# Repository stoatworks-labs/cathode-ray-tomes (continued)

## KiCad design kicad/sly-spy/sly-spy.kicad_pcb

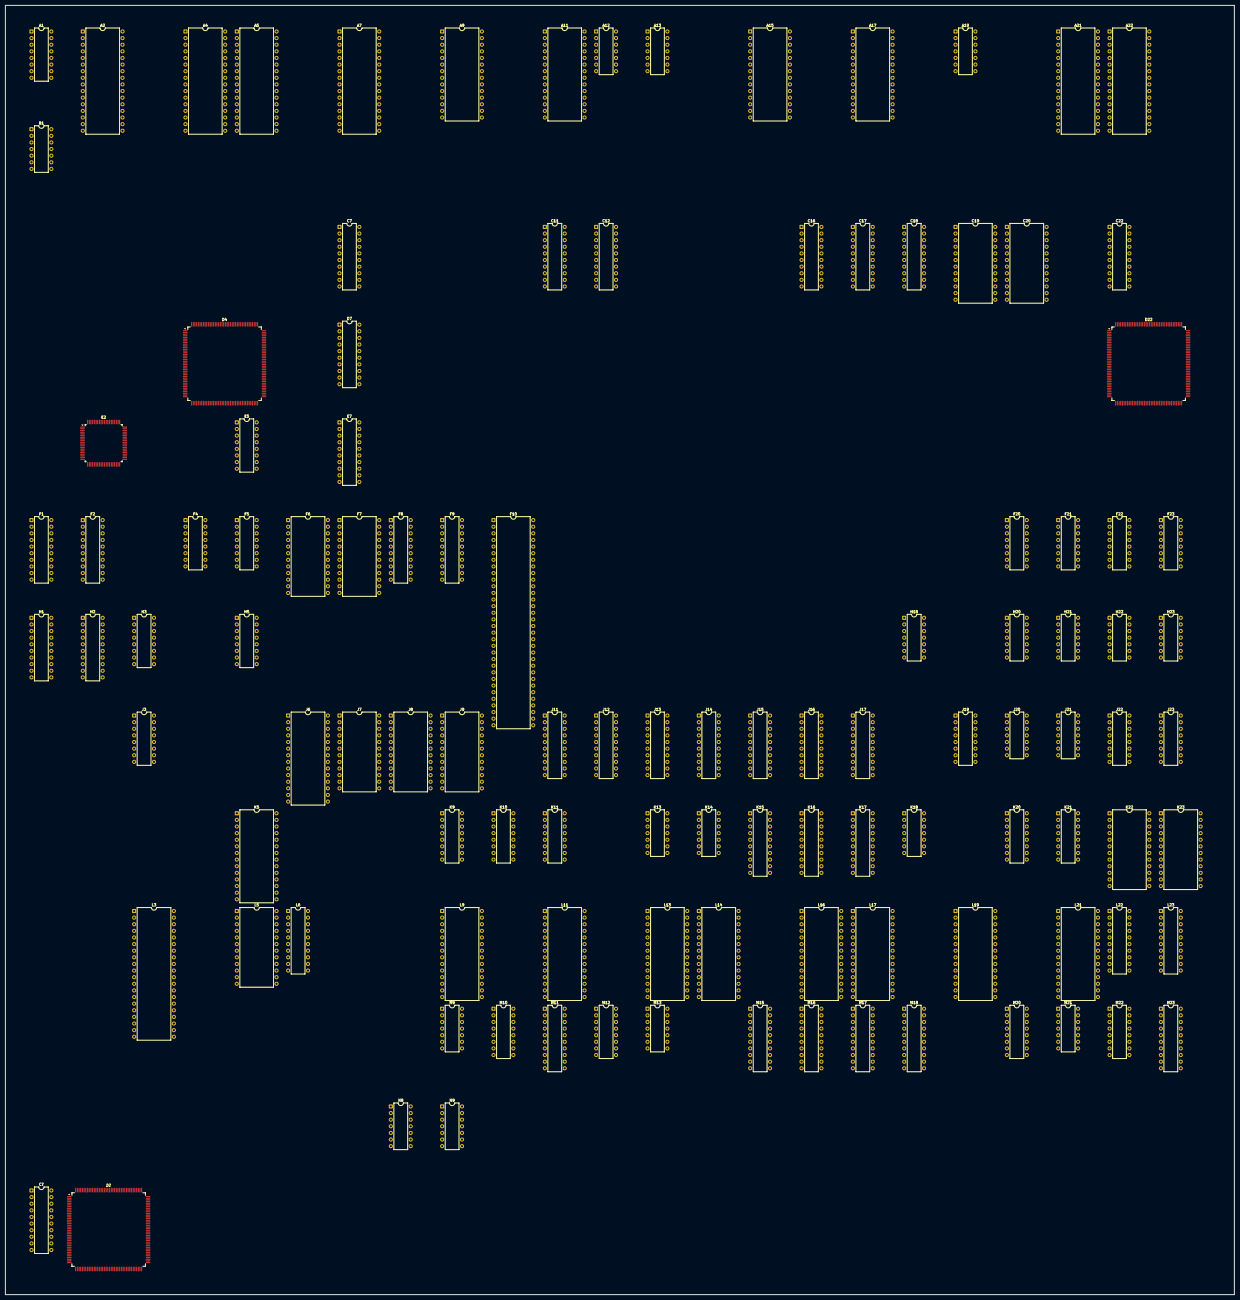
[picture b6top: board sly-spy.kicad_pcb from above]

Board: 2 copper layers, 471.6 x 494.7 mm, 113 parts (0 on the bottom side), 611 nets, no tracks yet.

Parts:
A1: 74LS390; DIP-16_W7.62mm
A2, A4, A5, A7, A21, A22: TC541001P; DIP-32_W15.24mm
A9, A11: 27256; DIP-28_W15.24mm
A12: 74LS08; DIP-14_W7.62mm
A13: 74xx04; DIP-14_W7.62mm
A15, A17: 27512; DIP-28_W15.24mm
A19: 74LS04; DIP-14_W7.62mm
B1: 74LS08; DIP-14_W7.62mm
C7: 74LS373; DIP-20_W7.62mm
C11, C12, C16, C17, C18, C22: 74LS273; DIP-20_W7.62mm
C19, C20: CXK5816; DIP-24_W15.24mm
C?: 74LS273; DIP-20_W7.62mm
D4: MXC_06; PQFP-160_28x28mm_P0.65mm
D7: 74LS373; DIP-20_W7.62mm
D22: BAC06; PQFP-160_28x28mm_P0.65mm
D?: BAC06; PQFP-160_28x28mm_P0.65mm
E2: HuC6280; PQFP-80_14x14mm_P0.65mm
E5: 74LS157; DIP-16_W7.62mm
E7: 74LS273; DIP-20_W7.62mm
F1, F2: 74LS245; DIP-20_W7.62mm
F4, F5: 74LS157; DIP-16_W7.62mm
F6, F7: TMM2018_25_35_45; DIP-24_W15.24mm
F8, F9: 74LS374; DIP-20_W7.62mm
F10: 68000D; DIP-64_W15.24mm
F20, F21, F22, F23: 74LS153; DIP-16_W7.62mm
H1, H2: 74LS245; DIP-20_W7.62mm
H3: 74LS138; DIP-16_W7.62mm
H5: 74LS139; DIP-16_W7.62mm
H18: 74LS74; DIP-14_W7.62mm
H20: 7425; DIP-14_W7.62mm
H21, H22: 74LS05; DIP-14_W7.62mm
H23: 74LS32; DIP-14_W7.62mm
J3: 74LS139; DIP-16_W7.62mm
J6: 27512; DIP-28_W15.24mm
J7, J8, J9: CXK5816; DIP-24_W15.24mm
J11, J12, J16, J17: 74LS245; DIP-20_W7.62mm
J13, J14, J15: 74LS244; DIP-20_W7.62mm
J19: 74LS367; DIP-16_W7.62mm
J20: 74LS74; DIP-14_W7.62mm
J21: 7425; DIP-14_W7.62mm
J22, J23: 74LS157; DIP-16_W7.62mm
K5: 368917K9; DIP-28_W15.24mm
K9, K10, K11, K20: 74LS157; DIP-16_W7.62mm
K13, K18: 74LS32; DIP-14_W7.62mm
K14: 74LS74; DIP-14_W7.62mm
K15, K17: PAL16L8; DIP-20_W7.62mm
K16: PAL16R4ACN; DIP-20_W7.62mm
K21: MB7114H; DIP-16_W7.62mm
K22, K23: TMM2018_25_35_45; DIP-24_W15.24mm
L3: YM2203; DIP-40_W15.24mm
L5: YM3812; DIP-24_W15.24mm
L6: 74LS374; DIP-20_W7.62mm
L9, L11, L13, L17, L19, L21: 27512; DIP-28_W15.24mm
L14, L16: TMM2063AP_10; DIP-28_W15.24mm
L22, L23: 74LS245; DIP-20_W7.62mm
M9: 74LS74; DIP-14_W7.62mm
M10: 74LS155; DIP-16_W7.62mm
M11: PAL16L8; DIP-20_W7.62mm
M12: 74LS138; DIP-16_W7.62mm
M13: 74LS10; DIP-14_W7.62mm
M15, M16, M17, M18: 74LS244; DIP-20_W7.62mm
M20: 74LS367; DIP-16_W7.62mm
M21: 74LS04; DIP-14_W7.62mm
M22: 74LS174; DIP-16_W7.62mm
M23: 74LS273; DIP-20_W7.62mm
N8: 74LS04; DIP-14_W7.62mm
N9: 74xx74; DIP-14_W7.62mm

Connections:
/MAINAB1: J13.18, J23.2, K11.2, L9.10, L11.10, L13.10, L14.10, L16.10, L17.10, L19.10, L21.10, M10.13
/MAINAB2: J13.12, J23.5, K11.5, L9.9, L11.9, L13.9, L14.9, L16.9, L17.9, L19.9, L21.9, M10.3
/MAINAB3: J13.9, J23.14, K11.11, L9.8, L11.8, L13.8, L14.8, L16.8, L17.8, L19.8, L21.8
/MAINAB4: J13.3, J23.11, K11.14, L9.7, L11.7, L13.7, L14.7, L16.7, L17.7, L19.7, L21.7
/MAINAB5: J13.5, J22.2, K10.2, L9.6, L11.6, L13.6, L14.6, L16.6, L17.6, L19.6, L21.6
/MAINAB6: J13.7, J22.5, K10.5, L9.5, L11.5, L13.5, L14.5, L16.5, L17.5, L19.5, L21.5
/MAINAB7: J13.14, J22.14, K10.11, L9.4, L11.4, L13.4, L14.4, L16.4, L17.4, L19.4, L21.4
/MAINAB8: J13.16, J22.11, K10.14, L9.3, L11.3, L13.3, L14.3, L16.3, L17.3, L19.3, L21.3
/MAINAB9: J14.9, K9.2, K20.2, L9.25, L11.25, L13.25, L14.25, L16.25, L17.25, L19.25, L21.25
/MAINAB10: J14.7, K9.5, K20.5, L9.24, L11.24, L13.24, L14.24, L16.24, L17.24, L19.24, L21.24
/colmix/A1: J23.4, K22.8, K23.8
/colmix/A2: J23.7, K22.7, K23.7
/colmix/A3: J23.12, K22.6, K23.6
/colmix/A4: J23.9, K22.5, K23.5
/colmix/A5: J22.4, K22.4, K23.4
/colmix/A6: J22.7, K22.3, K23.3
/colmix/A7: J22.12, K22.2, K23.2
/colmix/A8: J22.9, K22.1, K23.1
/colmix/A9: K20.4, K22.23, K23.23
/colmix/A10: K20.7, K22.22, K23.22
/colmix/A11: K20.12, K22.19, K23.19
/colmix/COL0: K23.9, L23.2, M23.18
/colmix/COL1: K23.10, L23.3, M23.17
/colmix/COL2: K23.11, L23.4, M23.14
/colmix/COL3: K23.13, L23.5, M23.13
/colmix/COL4: K23.14, L23.6, M23.8
/colmix/COL5: K23.15, L23.7, M23.7
/colmix/COL6: K23.16, L23.8, M23.4
/colmix/COL7: K23.17, L23.9, M23.3
/colmix/COL8: K22.9, L22.2, M22.6
/colmix/COL9: K22.10, L22.3, M22.4
/colmix/COL10: K22.11, L22.4, M22.3
/colmix/COL11: K22.13, L22.5, M22.11
/colmix/COL12: K22.14, L22.6
/colmix/COL13: K22.15, L22.7
/colmix/COL14: K22.16, L22.8
/colmix/COL15: K22.17, L22.9
/colmix/GFX1A0: F23.6, H20.5
/colmix/GFX1A1: F23.10, H20.1
/colmix/GFX1A2: F22.10, H20.2
/colmix/GFX1A3: F22.6, H20.4
/colmix/GFX1A4: C?.12, F21.6
/colmix/GFX1A7: F20.6, F20.10
/colmix/GFX1_BLANK: H20.6, K21.5
/colmix/GFX2A0: C16.2, F23.4, H20.13
/colmix/GFX2A1: C16.5, F23.12, H20.12
/colmix/GFX2A2: C16.6, F22.12, H20.10
/colmix/GFX2A3: C16.9, F22.4, K21.1
/colmix/GFX2A4: C16.12, F21.4
/colmix/GFX2A5: C16.15, F21.12
/colmix/GFX2A7: C16.19, F20.4, F20.12, K21.3
/colmix/GFX2_BLANK: H20.8, K21.7
/colmix/GFX3A0: F23.3, J21.13
/colmix/GFX3A1: F23.13, J21.12
/colmix/GFX3A2: F22.13, J21.10
/colmix/GFX3A3: F22.3, J21.9
/colmix/GFX3A4: C20.12, F21.3
/colmix/GFX3A7: F20.3, F20.13
/colmix/GFX3_BLANK: J21.8, K21.4
/colmix/OBJ0: E7.2, F23.5, J21.1
/colmix/OBJ1: E7.5, F23.11, J21.2
/colmix/OBJ2: E7.6, F22.11, J21.4
/colmix/OBJ3: E7.9, F22.5, J21.5
/colmix/OBJ4: E7.12, F21.5
/colmix/OBJ5: E7.15, F21.11
/colmix/OBJ7: E7.19, F20.5, F20.11
/colmix/OBJ_BLANK: J21.6, K21.6
/colmix/OBJ_COL10: D4.107, E7.4
/colmix/OBJ_COL20: D4.110, E7.7
/colmix/OBJ_COL30: D4.111, E7.8
/colmix/OBJ_COL40: D4.112, E7.13
/colmix/OBJ_COL50: D4.115, E7.14
/colmix/OBJ_COL60: D4.116, E7.17
/colmix/OBJ_COL76: D4.119, E7.18
/colmix/PRIO: H18.5, K21.2
/colmix/PXLCLK: A13.2, C16.11, E7.11, M22.9, M23.11
/colmix/S0: F20.14, F21.14, F22.14, F23.14, K20.3, K21.12
/colmix/S1: F20.2, F21.2, F22.2, F23.2, K20.6, K21.11
/colmix/VSS: F20.1, F20.15, F21.1, F21.15, F22.1, F22.15, F23.1, F23.15, H20.9, J22.15, J23.15, K20.10, K20.13, K20.15, K21.13, K21.14, K21.15, K22.20, K23.20
/colmix/~BLANK: H18.9, M22.1, M23.1
/colmix/~CS: K20.9, K22.18, K23.18
/colmix/~PALCS: H23.2, H23.5, H23.10, H23.13, J22.1, J23.1, K20.1, K20.11, M11.15
/gfx1_2.sch/B1MAPAD0: C?.8, D?.94
/gfx1_2.sch/B1MAPAD1: C?.7, D?.92
/gfx1_2.sch/B1MAPAD2: C?.6, D?.91
/gfx1_2.sch/B1MAPAD3: C?.5, D?.90
/gfx1_2.sch/B1MAPAD4: C?.4, D?.89
/gfx1_2.sch/B1MAPAD5: C?.3, D?.88
/gfx1_2.sch/B1MAPAD10: C?.19, D?.95
/gfx1_2.sch/B1MAPDB2: C?.11, D?.72
/gfx1_2.sch/B1MAPDB3: C?.13, D?.71
/gfx1_2.sch/B1MAPDB4: C?.14, D?.70
/gfx1_2.sch/B1MAPDB5: C?.15, D?.68
/gfx1_2.sch/B1MAPDB6: C?.16, D?.67
/gfx1_2.sch/B1MAPDB7: C?.17, D?.66
/gfx1_2.sch/B1MAPDB8: C?.9, D?.65
/gfx1_2.sch/B1MAPDB9: C?.10, D?.64
/gfx1_2.sch/BA0CGAD0: A11.19, C12.13
/gfx1_2.sch/BA0CGAD1: A11.18, C12.14
/gfx1_2.sch/BA0CGAD2: A11.17, C12.17
/gfx1_2.sch/BA0CGAD3: A11.16, C12.18
/gfx1_2.sch/BA0CGAD4: A11.15, C12.3
/gfx1_2.sch/BA0CGAD5: A11.13, C12.4
/gfx1_2.sch/BA0CGAD6: A11.12, C12.7
/gfx1_2.sch/BA0CGAD7: A11.11, C12.8
/gfx1_2.sch/BA0CGAD8: A9.19, C11.13
/gfx1_2.sch/BA0CGAD9: A9.18, C11.14
/gfx1_2.sch/BA0CGAD10: A9.17, C11.17
/gfx1_2.sch/BA0CGAD11: A9.16, C11.18
/gfx1_2.sch/BA0CGAD12: A9.15, C11.3
/gfx1_2.sch/BA0CGAD13: A9.13, C11.4
/gfx1_2.sch/BA0CGAD14: A9.12, C11.7
/gfx1_2.sch/BA0CGAD15: A9.11, C11.8
/gfx1_2.sch/BA1CGAD0: A17.19, C18.13, D?.23
/gfx1_2.sch/BA1CGAD1: A17.18, C18.14, D?.24
/gfx1_2.sch/BA1CGAD2: A17.17, C18.17, D?.25
/gfx1_2.sch/BA1CGAD3: A17.16, C18.18, D?.26
/gfx1_2.sch/BA1CGAD4: A17.15, C18.3, D?.27
/gfx1_2.sch/BA1CGAD5: A17.13, C18.4, D?.29
/gfx1_2.sch/BA1CGAD6: A17.12, C18.7, D?.30
/gfx1_2.sch/BA1CGAD7: A17.11, C18.8, D?.31
/gfx1_2.sch/BA1CGAD8: A15.19, C17.13, D?.32
/gfx1_2.sch/BA1CGAD9: A15.18, C17.14, D?.34
/gfx1_2.sch/BA1CGAD10: A15.17, C17.17, D?.35
/gfx1_2.sch/BA1CGAD11: A15.16, C17.18, D?.36
/gfx1_2.sch/BA1CGAD12: A15.15, C17.3, D?.37
/gfx1_2.sch/BA1CGAD13: A15.13, C17.4, D?.38
/gfx1_2.sch/BA1CGAD14: A15.12, C17.7, D?.39
/gfx1_2.sch/BA1CGAD15: A15.11, C17.8, D?.40
/gfx1_2.sch/BA1_133: A13.9, D?.133
/gfx1_2.sch/BA1_136: A13.5, D?.136
/gfx1_2.sch/BA1_138: D?.138, L5.24
/gfx1_2.sch/BA1_155: D?.155, H18.12
/gfx1_2.sch/BA1_CGSEL0: A12.5, D?.44
/gfx1_2.sch/BA1_NMAPSEL: D?.124, M12.12
/gfx1_2.sch/BA1_NMODE: D?.122, M12.15
/gfx1_2.sch/BA1_NSIFT: D?.123, M12.14
/gfx1_2.sch/BA1_~NRAMRD: C?.20, D?.98
/gfx1_2.sch/BA_~BUDS: D?.125, K17.12
/gfx1_2.sch/VCC: D?.19, D?.41, D?.49, D?.50, D?.62, D?.81, D?.102, D?.121, D?.140, D?.160
/gfx1_2.sch/VLOAD_IN: D?.157, N9.12
/gfx1_2.sch/VSS: C?.18, D?.12, D?.14, D?.20, D?.21, D?.22, D?.33, D?.47, D?.48, D?.51, D?.52, D?.59, D?.60, D?.61, D?.74, D?.87, D?.99
/gfx3/B2MAPAD0: C19.8, C20.8, D22.94
/gfx3/B2MAPAD1: C19.7, C20.7, D22.92
/gfx3/B2MAPAD2: C19.6, C20.6, D22.91
/gfx3/B2MAPAD3: C19.5, C20.5, D22.90
/gfx3/B2MAPAD4: C19.4, C20.4, D22.89
/gfx3/B2MAPAD5: C19.3, C20.3, D22.88
/gfx3/B2MAPAD6: C19.2, C20.2, D22.86
/gfx3/B2MAPAD7: C19.1, D22.85
/gfx3/B2MAPAD8: C19.23, C20.23, D22.84
/gfx3/B2MAPAD9: C19.22, C20.22, D22.83
/gfx3/B2MAPAD10: C19.19, C20.19, D22.95
/gfx3/B2MAPDB0: C20.9, D22.75
/gfx3/B2MAPDB1: C20.10, D22.73
/gfx3/B2MAPDB2: C20.11, D22.72
/gfx3/B2MAPDB3: C20.13, D22.71
/gfx3/B2MAPDB4: C20.14, D22.70
/gfx3/B2MAPDB5: C20.15, D22.68
/gfx3/B2MAPDB6: C20.16, D22.67
/gfx3/B2MAPDB7: C20.17, D22.66
/gfx3/B2MAPDB8: C19.9, D22.65
/gfx3/B2MAPDB9: C19.10, D22.64
/gfx3/B2MAPDB10: C19.11, D22.63
/gfx3/B2MAPDB11: C19.13, D22.58
/gfx3/B2MAPDB12: C19.14, D22.57
/gfx3/B2MAPDB13: C19.15, D22.56
/gfx3/B2MAPDB14: C19.16, D22.55
/gfx3/B2MAPDB15: C19.17, D22.54
/gfx3/BA2CGAD0: A22.21, D22.23
/gfx3/BA2CGAD1: A22.20, D22.24
/gfx3/BA2CGAD2: A22.19, D22.25
/gfx3/BA2CGAD3: A22.18, D22.26
/gfx3/BA2CGAD4: A22.17, D22.27
/gfx3/BA2CGAD5: A22.15, D22.29
/gfx3/BA2CGAD6: A22.14, D22.30
/gfx3/BA2CGAD7: A22.13, D22.31
/gfx3/BA2CGAD8: A21.21, C22.13, D22.32
/gfx3/BA2CGAD9: A21.20, C22.14, D22.34
/gfx3/BA2CGAD10: A21.19, C22.17, D22.35
/gfx3/BA2CGAD11: A21.18, C22.18, D22.36
/gfx3/BA2CGAD12: A21.17, C22.3, D22.37
/gfx3/BA2CGAD13: A21.15, C22.4, D22.38
/gfx3/BA2CGAD14: A21.14, C22.7, D22.39
/gfx3/BA2CGAD15: A21.13, C22.8, D22.40
/gfx3/BA2_CGSEL0: A13.1, D22.44, H18.11
/gfx3/BA2_NMAPSEL: D22.124, H5.6, M12.7
/gfx3/BA2_NMODE: D22.122, K13.3, M12.11
/gfx3/BA2_NSIFT: D22.123, H5.5
/gfx3/BA2_~BLDS: D22.126, K18.3
/gfx3/BA2_~BUDS: D22.125, K18.11
/gfx3/BA2_~NRAMRD: C19.20, C20.20, D22.98
/gfx3/BA2_~NRAMWRH: C19.21, D22.96
/gfx3/BA2_~NRAMWRL: C20.21, D22.97
/gfx3/VCC: D22.19, D22.41, D22.49, D22.50, D22.62, D22.81, D22.102, D22.121, D22.140, D22.160
/gfx3/VSS: C19.18, C20.18, D22.12, D22.14, D22.20, D22.21, D22.22, D22.33, D22.47, D22.48, D22.51, D22.52, D22.59, D22.60, D22.61, D22.74, D22.87, D22.99
/gfxrom/A0: A2.12, A4.12, A5.12, A7.12, D7.2
/gfxrom/A1: A2.11, A4.11, A5.11, A7.11, D7.5
/gfxrom/A2: A2.10, A4.10, A5.10, A7.10, D7.6
/gfxrom/A3: A2.9, A4.9, A5.9, A7.9, D7.9
/gfxrom/A4: A2.8, A4.8, A5.8, A7.8
/gfxrom/A5: A2.7, A4.7, A5.7, A7.7, D7.12
/gfxrom/A6: A2.6, A4.6, A5.6, A7.6, D7.15
/gfxrom/A7: A2.5, A4.5, A5.5, A7.5, D7.16
/gfxrom/A8: A2.27, A4.27, A5.27, A7.27, D7.19
/gfxrom/A9: A2.26, A4.26, A5.26, A7.26, C7.2
/gfxrom/A10: A2.23, A4.23, A5.23, A7.23, C7.5
/gfxrom/A11: A2.25, A4.25, A5.25, A7.25, C7.6
/gfxrom/A12: A2.4, A4.4, A5.4, A7.4, C7.9
/gfxrom/A13: A2.28, A4.28, A5.28, A7.28, C7.12
/gfxrom/A14: A2.29, A4.29, A5.29, A7.29, C7.15
/gfxrom/A15: A2.3, A4.3, A5.3, A7.3, C7.16
/gfxrom/BA0_CGADLD: C11.11, C12.11, D?.43
/gfxrom/BA0_CGSEL1: A9.27, A11.27, A12.13
/gfxrom/BA1_CGSEL1: A12.4, A15.1, A17.1, D?.45
/gfxrom/BA1_CGSELD: C17.11, C18.11
/gfxrom/BA2_CGADLD: C22.11, D22.43
/gfxrom/BA2_CGSEL1: A12.2, A21.24, A22.24, D22.45
/gfxrom/CGAD0: A2.13, D4.130
/gfxrom/CGAD1: A2.14, D4.131
/gfxrom/CGAD2: A2.15, D4.132
/gfxrom/CGAD3: A2.17, D4.136
/gfxrom/CGAD4: A2.18, D4.137
/gfxrom/CGAD5: A2.19, D4.144
/gfxrom/CGAD6: A2.20, D4.147
/gfxrom/CGAD7: A2.21, D4.145
/gfxrom/CGAD8: A4.13, D4.151
/gfxrom/CGAD9: A4.14, D4.150
/gfxrom/CGAD10: A4.15, D4.155
/gfxrom/CGAD11: A4.17, D4.152
/gfxrom/CGAD12: A4.18, D4.159, D7.3
/gfxrom/CGAD13: A4.19, D4.156, D7.4
/gfxrom/CGAD14: A4.20, D4.2, D7.7
/gfxrom/CGAD15: A4.21, D4.157, D7.8
/gfxrom/CGAD16: A5.13, D4.160, D7.13
/gfxrom/CGAD17: A5.14, D4.3, D7.14
/gfxrom/CGAD18: A5.15, D4.5, D7.17
/gfxrom/CGAD19: A5.17, D4.6, D7.18
/gfxrom/CGAD20: A5.18, C7.3, D4.7
/gfxrom/CGAD21: A5.19, C7.4, D4.10
/gfxrom/CGAD22: A5.20, C7.7, D4.11
/gfxrom/CGAD23: A5.21, C7.8, D4.12
/gfxrom/CGAD24: A7.13, C7.13, D4.16
/gfxrom/CGAD25: A7.14, C7.14, D4.17
/gfxrom/CGAD26: A7.15, C7.17, D4.23
/gfxrom/CGAD27: A7.17, C7.18, D4.25
/gfxrom/CGAD28: A7.18, D4.28
/gfxrom/CGAD29: A7.19, D4.31
/gfxrom/CGAD30: A7.20, D4.30
/gfxrom/CGAD31: A7.21, D4.32
/gfxrom/CGADL: C7.11, D4.84, D7.11
/gfxrom/NCGR0: B1.5, D4.90
/gfxrom/NCGR1: B1.4, D4.87
/gfxrom/X0: A21.12, A22.12, C22.12
/gfxrom/X1: A21.11, A22.11, C22.15
/gfxrom/X2: A21.10, A22.10, C22.16
/gfxrom/X3: A21.9, A22.9, C22.19
/gfxrom/X4: A19.4, A21.8, A22.8
/gfxrom/X5: A21.7, A22.7, C22.5
/gfxrom/X6: A21.6, A22.6, C22.6
/gfxrom/X7: A21.5, A22.5, C22.9
/gfxrom/X8: A21.27, A22.27
/gfxrom/X9: A21.26, A22.26
/gfxrom/X10: A21.23, A22.23
/gfxrom/X11: A21.25, A22.25
/gfxrom/X12: A21.4, A22.4
/gfxrom/X13: A21.28, A22.28
/gfxrom/X14: A21.29, A22.29
/gfxrom/X15: A21.3, A22.3
/gfxrom/Y0: A15.10, A17.10, C17.12
/gfxrom/Y1: A15.9, A17.9, C17.15
/gfxrom/Y2: A15.8, A17.8, C17.16
/gfxrom/Y3: A15.7, A17.7, C17.19
/gfxrom/Y4: A15.6, A17.6, A19.12
/gfxrom/Y5: A15.5, A17.5, C17.5
/gfxrom/Y6: A15.4, A17.4, C17.6
/gfxrom/Y7: A15.3, A17.3, C17.9
/gfxrom/Y8: A15.25, A17.25, C18.12
/gfxrom/Y9: A15.24, A17.24, C18.15
/gfxrom/Y10: A15.21, A17.21, C18.16
/gfxrom/Y11: A15.23, A17.23, C18.19
/gfxrom/Y12: A15.2, A17.2, C18.2
/gfxrom/Y13: A15.26, A17.26, C18.5
/gfxrom/Y14: A15.27, A17.27, C18.6
/gfxrom/Z0: A9.10, A11.10, C11.12
/gfxrom/Z1: A9.9, A11.9, C11.15
/gfxrom/Z2: A9.8, A11.8, C11.16
/gfxrom/Z3: A9.7, A11.7, C11.19
/gfxrom/Z4: A9.6, A11.6, C11.2
/gfxrom/Z5: A9.5, A11.5, C11.5
/gfxrom/Z6: A9.4, A11.4, C11.6
/gfxrom/Z7: A9.3, A11.3, C11.9
/gfxrom/Z8: A9.25, A11.25, C12.12
/gfxrom/Z9: A9.24, A11.24, C12.15
/gfxrom/Z10: A9.21, A11.21, C12.16
/gfxrom/Z11: A9.23, A11.23, C12.19
/gfxrom/Z12: A9.2, A11.2, C12.2
/gfxrom/Z13: A9.26, A11.26, C12.5
/gfxrom/~CEGFX: A4.22, A5.22, A7.22
/gfxrom/~CEX: A12.3, A21.22, A22.22
/gfxrom/~CE_GFX: A2.22, B1.6
/gfxrom/~OEY: A12.6, A15.22, A17.22
/gfxrom/~OEZ: A9.22, A11.22, A12.11
/gfxrom/~OE: A2.24, A4.24, A5.24, A7.24, C7.19
/main/A1: F10.29, J13.2
/main/A2: F10.30, J13.8
/main/A3: F10.31, J13.11
/main/A4: F10.32, J13.17
/main/A5: F10.33, J13.15
/main/A6: F10.34, J13.13
/main/A7: F10.35, J13.6
/main/A8: F10.36, J13.4
/main/A9: F10.37, J14.11
/main/A10: F10.38, J14.13
/main/A11: F10.39, J14.15
/main/A12: F10.40, J14.17
/main/A13: F10.41, J14.8
/main/A14: F10.42, J14.6
/main/A15: F10.43, J14.4
/main/A16: F10.44, J14.2
/main/A17: F10.45, J15.11
/main/A18: F10.46, J15.13
/main/A19: F10.47, J15.15
/main/A20: F10.48, J15.17
/main/A21: F10.50, J15.8
/main/AS: K14.3, K14.10, M21.6
/main/BA1_VCNT: D4.124, D?.144, M11.8, N9.11
/main/CEC: J17.19, K18.8
/main/CED: J16.19, K18.6
/main/CLK: F10.15, J20.2, J20.6, K16.1, L6.11, M10.9
/main/CLK_MAIN: A1.12, J20.5
/main/D0: F10.5, J17.11, L16.11
/main/D1: F10.4, J17.12, L16.12
/main/D2: F10.3, J17.13, L16.13
/main/D3: F10.2, J17.14, L16.15
/main/D4: F10.1, J17.15, L16.16
/main/D5: F10.64, J17.16, L16.17
/main/D6: F10.63, J17.17, L16.18
/main/D7: F10.62, J17.18, L16.19
/main/D8: F10.61, J16.11, L14.11
/main/D9: F10.60, J16.12, L14.12
/main/D10: F10.59, J16.13, L14.13
/main/D11: F10.58, J16.14, L14.15
/main/D12: F10.57, J16.15, L14.16
/main/D13: F10.56, J16.16, L14.17
/main/D14: F10.55, J16.17, L14.18
/main/D15: F10.54, J16.18, L14.19
/main/DB0: J11.18, J17.9, L6.3, L9.11, L11.11, L13.11, L23.18, M17.3, M18.3, M20.5
/main/DB1: J11.17, J17.8, K17.8, K18.9, K18.12, L6.4, L9.12, L11.12, L13.12, L23.17, M17.5, M18.5, M20.7
/main/DB2: J11.16, J17.7, L6.7, L9.13, L11.13, L13.13, L23.16, M17.7, M18.7, M20.9
/main/DB3: J11.15, J17.6, L6.8, L9.15, L11.15, L13.15, L23.15, M17.9, M18.9, M20.3
/main/DB4: J11.14, J17.5, L6.18, L9.16, L11.16, L13.16, L23.14, M17.12, M18.12
/main/DB5: J11.13, J17.4, L6.17, L9.17, L11.17, L13.17, L23.13, M17.14, M18.14
/main/DB6: J11.12, J17.3, L6.14, L9.18, L11.18, L13.18, L23.12, M17.16, M18.16
/main/DB7: H18.2, J11.11, J17.2, L6.13, L9.19, L11.19, L13.19, L23.11, M17.18, M18.18
/main/DB8: J12.18, J16.9, L17.11, L19.11, L21.11, L22.18, M15.3, M16.3
/main/DB9: J12.17, J16.8, L17.12, L19.12, L21.12, L22.17, M15.5, M16.5
/main/DB10: J12.16, J16.7, L17.13, L19.13, L21.13, L22.16, M15.7, M16.7
/main/DB11: J12.15, J16.6, L17.15, L19.15, L21.15, L22.15, M15.9, M16.9
/main/DB12: J12.14, J16.5, L17.16, L19.16, L21.16, L22.14, M15.12, M16.12
/main/DB13: J12.13, J16.4, L17.17, L19.17, L21.17, L22.13, M15.14, M16.14
/main/DB14: J12.12, J16.3, L17.18, L19.18, L21.18, L22.12, M15.16, M16.16
/main/DB15: J12.11, J16.2, L17.19, L19.19, L21.19, L22.11, M15.18, M16.18
/main/DEC0: K16.18, K17.2
/main/DEC1: K16.15, K17.1
/main/DEC2: K16.13, M11.5
/main/DEC3: K16.12, K17.3
/main/DEC4: M10.2, M10.14, M11.19
/main/DEC5: H5.1, K18.2, K18.13, M11.18
/main/DSPLD: D4.127, M11.13
/main/EDLD: D4.117, M11.12
/main/FC0: F10.28, M13.3
/main/FC1: F10.27, M13.4
/main/FC2: F10.26, M13.5
/main/L_R: K16.19, K17.11, M11.4, M12.5
/main/MAIN0: H5.12, K16.4
/main/MAINAB11: H5.2, J14.5, L9.21, L11.21, L13.21, L14.21, L16.21, L17.21, L19.21, L21.21
/main/MAINAB12: H5.3, J14.3, L9.23, L11.23, L13.23, L14.23, L16.23, L17.23, L19.23, L21.23
/main/MAINAB13: H5.15, J14.12, L9.2, L11.2, L13.2, L14.2, L16.2, L17.2, L19.2, L21.2, M12.1
/main/MAINAB14: H5.13, J14.14, L9.26, L11.26, L13.26, L17.26, L19.26, L21.26, M11.1, M12.2
/main/MAINAB15: J14.16, L9.27, L11.27, L13.27, L17.27, L19.27, L21.27, M11.2, M12.3
/main/MAINAB16: H5.14, J14.18, L9.1, L11.1, L13.1, L17.1, L19.1, L21.1, M11.3
/main/MAINAB17: J15.9, K15.1
/main/MAINAB18: J15.7, K15.2, M12.6
/main/MAINAB19: J15.5, K15.3, M12.4
/main/MAINAB20: J15.3, K15.4, K16.8
/main/MAINAB21: J15.12, K15.5, K16.9
/main/MAINAQ1: M10.6, M16.19, M17.19
/main/MAINAQ2: M10.5, M20.1
/main/MAINGFX0: H5.4, K13.2
/main/NVLOAD: D4.125, N9.9
/main/OSC: E2.10, K14.11
/main/OSCQ: K14.9, K17.4
/main/R~W: D22.127, F10.9, J19.6, K17.19
/main/R~W_B: J11.1, J12.1, J16.1, J17.1, J19.7, K15.6, K17.6, M10.1, M10.15
/main/R~W_O: M10.7, M15.1, M18.1
/main/SA: K9.1, K10.1, K11.1, K13.5, K13.10
/main/mainmem/CS2: L14.26, L16.26
/main/mainmem/~OEB: L9.22, L14.22
/main/~ASl: K14.6, K16.3
/main/~AS: F10.6, J19.2
/main/~AS_B: J19.3, K13.13, K16.2, K17.5, M21.5
/main/~CS1_B: K18.5, K18.10, M21.12
/main/~CS1: L14.20, L16.20, M11.17, M21.13
/main/~DTACK: F10.10, K17.18
/main/~HALT: F10.17, H22.4
/main/~LDS: F10.8, J19.10
/main/~LDS_B: H23.9, J19.9, K13.1, K15.7
/main/~OEA: K15.13, K17.15, L13.22, L16.22, M21.1
/main/~PRIOCS: H18.3, M10.10
/main/~RESET: F10.18, H22.2
/main/~UDS: F10.7, J19.4
/main/~UDS_B: H23.4, J19.5, K15.8, K17.9, K18.1, K18.4
/main/~VPA: F10.21, K13.11
/main/~WEA: J8.21, K13.8
/main/~WEB: J9.21, K13.6
/main/~WEL: A12.1, H23.12, K13.9, K17.17
/main/~WEU: H23.1, K13.4, K17.16
/objects/M2M: A13.11, D4.79
/objects/MATAB0: D4.57, F5.2
/objects/MATAB1: D4.55, F5.5
/objects/MATAB2: D4.54, F5.14
/objects/MATAB3: D4.63, F5.11
/objects/MATAB4: D4.64, F4.2
/objects/MATAB5: D4.65, F4.5
/objects/MATAB6: D4.68, F4.14
/objects/MATAB7: D4.69, F4.11
/objects/MATAB8: D4.71, E5.2
/objects/MATAB9: D4.72, E5.5
/objects/MATAB10: D4.75, E5.11
/objects/MATDB0: D4.40, F7.9, F8.2
/objects/MATDB1: D4.37, F7.10, F8.5
/objects/MATDB2: D4.36, F7.13, F8.9
/objects/MATDB3: D4.43, F7.11, F8.6
/objects/MATDB4: D4.42, F7.14, F8.12
/objects/MATDB5: D4.39, F7.15, F8.15
/objects/MATDB6: D4.35, F7.16, F8.16
/objects/MATDB7: D4.46, F7.17, F8.19
/objects/MATDB8: D4.45, F6.9, F9.2
/objects/MATDB9: D4.41, F6.10, F9.5
/objects/MATDB10: D4.38, F6.11, F9.6
/objects/MATDB11: D4.50, F6.13, F9.9
/objects/MATDB12: D4.47, F6.14, F9.12
/objects/MATDB13: D4.44, F6.15, F9.15
/objects/MATDB14: D4.52, F6.16, F9.16
/objects/MATDB15: D4.51, F6.17, F9.19
/objects/VCC: D4.1, D4.19, D4.58, D4.62, D4.77, D4.78, D4.80, D4.81, D4.82, D4.83, D4.99, D4.102, D4.139
/objects/VSS: D4.4, D4.8, D4.9, D4.14, D4.20, D4.21, D4.27, D4.33, D4.34, D4.48, D4.49, D4.60, D4.61, D4.73, D4.88, D4.89, D4.94, D4.100, D4.101, D4.113, D4.114, D4.118, D4.121, D4.129, D4.140, D4.141, D4.153, D4.154, D4.158
/objram/A0: F5.4, F6.8, F7.8
/objram/A1: F5.7, F6.7, F7.7
/objram/A2: F5.12, F6.5, F7.5
/objram/A3: F5.9, F6.6, F7.6
/objram/A4: F4.4, F6.4, F7.4
/objram/A5: F4.7, F6.3, F7.3
/objram/A6: F4.12, F6.2, F7.2
/objram/A7: F4.9, F6.23, F7.23
/objram/A8: E5.4, F6.1, F7.1
/objram/A9: E5.7, F6.22, F7.22
/objram/AA0: J8.8, J9.8, K11.4
/objram/AA1: J8.7, J9.7, K11.7
/objram/AA2: J8.6, J9.6, K11.9
/objram/AA3: J8.5, J9.5, K11.12
/objram/AA4: J8.4, J9.4, K10.4
/objram/AA5: J8.3, J9.3, K10.7
/objram/AA6: J8.2, J9.2, K10.9
/objram/AA7: J8.1, J9.1, K10.12
/objram/AA8: J8.23, J9.23, K9.4
/objram/AA9: J8.22, J9.22, K9.7
/objram/AA10: J8.19, J9.19
/objram/CEA: J12.19, K9.12
/objram/CEB: J11.19, K9.9
/objram/CKL_JR: F8.11, F9.11, M9.3
/objram/DMADB0: F8.3, J8.9, J11.2
/objram/DMADB1: F8.4, J8.10, J11.3
/objram/DMADB2: F8.7, J8.11, J11.4
/objram/DMADB3: F8.8, J8.13, J11.5
/objram/DMADB4: F8.13, J8.14, J11.6
/objram/DMADB5: F8.14, J8.15, J11.7
/objram/DMADB6: F8.17, J8.16, J11.8
/objram/DMADB7: F8.18, J8.17, J11.9
/objram/DMADB8: F9.3, J9.9, J12.2
/objram/DMADB9: F9.4, J9.10, J12.3
/objram/DMADB10: F9.7, J9.11, J12.4
/objram/DMADB11: F9.8, J9.13, J12.5
/objram/DMADB12: F9.13, J9.14, J12.6
/objram/DMADB13: F9.14, J9.15, J12.7
/objram/DMADB14: F9.17, J9.16, J12.8
/objram/DMADB15: F9.18, J9.17, J12.9
/objram/I1A: F4.3, K10.3
/objram/I1B: F4.6, K10.6
/objram/I1C: F4.13, K10.13
/objram/I1CC: F5.13, K11.13
/objram/I1D: F4.10, K10.10
/objram/JR_I1AA: A13.6, F5.3, K11.3
/objram/JR_I1BB: A13.8, F5.6, K11.6
/objram/PIN20: E5.13, K9.13
/objram/PIN22: E5.6, K9.6
/objram/PIN23: E5.3, K9.3
/objram/SELECT: E5.1, F4.1, F5.1
/objram/VSS: E5.10, E5.15, F4.15, F5.10, F5.15, F6.19, F6.20, F7.19, F7.20, K9.15, K10.15, K11.10, K11.15
/objram/~CEH: J8.18, J9.18
/objram/~CS: E5.9, F6.18, F7.18
/objram/~OEH: J8.20, J9.20
/objram/~WE_OBJ: E5.12, F6.21, F7.21, F8.1, F9.1
/sound/A0: E2.6, H1.11
/sound/A1: E2.5, H1.12
/sound/A2: E2.4, H1.13
/sound/A3: E2.3, H1.14
/sound/A4: E2.2, H1.15
/sound/A5: E2.1, H1.16
/sound/A6: E2.80, H1.17
/sound/A7: E2.79, H1.18
/sound/A8: E2.78, F1.11
/sound/A9: E2.77, F1.12
/sound/A10: E2.74, F1.13
/sound/A11: E2.73, F1.14
/sound/A12: E2.72, F1.15
/sound/A13: E2.71, F1.16
/sound/A14: E2.70, F1.17
/sound/A15: E2.69, F1.18
/sound/A16: E2.68, F2.18
/sound/A17: E2.67, F2.17
/sound/A18: E2.66, F2.16
/sound/A19: E2.65, F2.15
/sound/A20: E2.64, F2.14
/sound/AB0: H1.9, J6.10, J7.8, L3.37, L5.4
/sound/AB1: H1.8, J6.9, J7.7
/sound/AB2: H1.7, J6.8, J7.6
/sound/AB3: H1.6, J6.7, J7.5
/sound/AB4: H1.5, J6.6, J7.4
/sound/AB5: H1.4, J6.5, J7.3
/sound/AB6: H1.3, J6.4, J7.2
/sound/AB7: H1.2, J6.3, J7.1
/sound/AB8: F1.9, J6.25, J7.23
/sound/AB9: F1.8, J6.24, J7.22
/sound/AB10: F1.7, J6.21, J7.19
/sound/AB11: F1.6, J6.23
/sound/AB12: F1.5, J6.2
/sound/AB13: F1.4, J6.26
/sound/AB14: F1.3, J6.27
/sound/AB15: F1.2, J6.1
/sound/AB16: F2.2, H3.1, J3.2
/sound/AB17: F2.3, H3.2, J3.3
/sound/AB18: F2.4, H3.3, J3.1
/sound/AB19: F2.5, H3.6, J3.14
/sound/AB20: F2.6, H3.5, J3.13
/sound/CEX_ROM: A13.4, M20.2
/sound/D0: E2.49, H2.18
/sound/D1: E2.50, H2.17
/sound/D2: E2.51, H2.16
/sound/D3: E2.52, H2.15
/sound/D4: E2.53, H2.14
/sound/D5: E2.54, H2.13
/sound/D6: E2.55, H2.12
/sound/D7: E2.56, H2.11
/sound/PHM: A13.10, L3.38, M9.11
/sound/PIN4: H3.9, L3.23
/sound/SDB0: H2.9, J6.11, J7.17, L3.8, L5.18, L6.12
/sound/SDB1: H2.8, J6.18, J7.16, L3.7, L5.17, L6.15
/sound/SDB2: H2.7, J6.17, J7.15, L3.6, L5.16, L6.16
/sound/SDB3: H2.6, J6.16, J7.14, L3.5, L5.15, L6.19
/sound/SDB4: H2.5, J6.15, J7.13, L3.4, L5.14, L6.9
/sound/SDB5: H2.4, J6.13, J7.11, L3.3, L5.13, L6.6
/sound/SDB6: H2.3, J6.12, J7.10, L3.2, L5.11, L6.5
/sound/SDB7: H2.2, J6.19, J7.9, L3.40, L5.10, L6.2
/sound/~CER: E2.61, J7.18
/sound/~CEY: A13.12, H2.19
/sound/~CE: J3.12, J6.20
/sound/~CS_OPL: H3.14, L5.7
/sound/~CS_OPN: H3.12, L3.34
/sound/~IC: A13.3, B1.9, L3.24, L5.3
/sound/~IRQ2: E2.43, L3.25, L5.2
/sound/~OE: H3.7, L6.1
/sound/~RDB: F2.8, J6.22, J7.20, L3.36, L5.6
/sound/~RD: E2.62, F2.12
/sound/~RESET: B1.8, E2.11
/sound/~WRB: F2.7, J7.21, L3.35, L5.5
/sound/~WR: E2.63, F2.13, H2.1
GND: A1.14, A2.1, A2.2, A2.16, A2.31, A2.32, A4.1, A4.2, A4.16, A4.31, A4.32, A5.1, A5.2, A5.16, A5.31, A5.32, A7.1, A7.2, A7.16, A7.31, A7.32, A9.1, A9.14, A9.20, A9.28, A11.1, A11.14, A11.20, A11.28, A15.14, A15.20, A15.28, A17.14, A17.20, A17.28, A21.1, A21.2, A21.16, A21.31, A21.32, A22.1, A22.16, A22.31, A22.32, C7.1, C11.1, C12.1, C16.1, C17.1, C18.1, C20.1, C22.1, C?.1, C?.2, D7.1, E2.57, E5.14, E7.1, F1.1, F1.19, F2.1, F2.19, F6.12, F6.24, F7.12, F7.24, F10.12, F10.13, F10.14, F10.16, F10.22, F10.49, F10.53, H1.1, H1.19, H3.4, H18.4, H18.10, H18.13, H20.3, H20.11, J13.1, J13.19, J14.1, J14.19, J15.1, J15.19, J19.1, J19.8, J19.16, J20.1, J20.4, J21.3, J21.11, K14.1, K14.4, K14.13, K15.10, K15.20, K16.10, K16.11, K16.20, K17.10, K17.20, K22.12, K22.24, K23.12, K23.24, L3.1, L14.14, L14.28, L16.14, L16.28, M9.1, M9.4, M9.13, M11.10, M11.20, M15.2, M15.4, M18.2, M18.4, M20.15, N9.7, N9.10, N9.13
Gnd: H20.7, J21.7
unnamed: A1.9, A1.15
unnamed: A19.13, C17.2
unnamed: A19.3, C22.2
unnamed: F20.7, J22.10
unnamed: F20.9, J22.13
unnamed: F21.7, J22.3
unnamed: F21.9, J22.6
unnamed: F22.7, J23.10
unnamed: F22.9, J23.13
unnamed: F23.7, J23.3
unnamed: F23.9, J23.6
unnamed: H18.1, H21.2
unnamed: H21.1, H21.6, H22.1, H22.3
unnamed: J3.4, J3.15
unnamed: K13.12, M13.6
unnamed: K14.12, M9.2, M9.9
unnamed: K16.14, M9.12
unnamed: K16.7, M9.8
unnamed: H23.3, K22.21
unnamed: H23.11, K23.21
unnamed: L22.1, L23.1
unnamed: H23.6, L22.19
unnamed: H23.8, L23.19
unnamed: M9.5, M9.10
unnamed: M15.10, M16.20
unnamed: M16.10, M17.20
unnamed: M17.10, M18.20
unnamed: M20.4, M21.11
unnamed: M20.6, M21.9
VDD: A13.14, E2.47, N9.14
Vcc: H20.14, J21.14

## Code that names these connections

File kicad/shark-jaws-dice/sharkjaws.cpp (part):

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/* signals */

//sync generator
 #define _CLOCKn  "4E", 6

 #define _1H "5D", 12
 #define _2H "5D", 9
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 #define _4Hn "4B", 2
 #define _256Hn "4D", 2

 #define _HRESETn "5A", 9
 #define _HRESET "5A", 8

 #define _HSYNC "5A", 6
 #define _HSYNCn "5A", 5
 #define _HSYNC1 "4B", 6

 #define _1V "5F", 12
 #define _2V "5F", 9
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 #define _256V "4D", 5
 #define _256Vn "4D", 6

 #define _VRESET "4E", 8
 #define _VRESETn "4E", 9

 #define _VSYNCn "4A", 6

 #define _HBLANK "7C", 6
 #define _HBLANKn "7C", 5

 #define _VBLANK "7C", 8
 #define _VBLANKn "7C", 9

 #define _COMPBLANK "8K", 8

//Score
 #define _SCOREWIN "7E", 4
 #define _FISHSCORE "C9A", 3  //555:3 = 556:5
 #define _SCORE "2L", 2
 #define _SCOREn "1E", 15

//Half second clock
 #define _HALFSEC "8B", 8
 #define _HALFSECn "4B", 8

//Coin/Start/Timer
 #define _ENDGAMEn "N9A", 3  //556 pin 5 = 555 pin 3

 #define _START "8E", 6
 #define _STARTn "8E", 5

 #define _ATTRACT "8E", 9
 #define _ATTRACTn "8E", 8

 #define _Q "8F", 8

 #define _CREDITn "8D", 9

//Small fish motion
 #define _SMLFISHDIR "8J", 2

 #define _CV1 "6N", 9
 #define _CV2 "1L", 14
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 #define _SH3 "1N", 12
 #define _SH4 "1N", 11

 #define _CVWIN "3M", 8
 #define _CHWIN "1N", 15

//Diver motion
 #define _STOPH  "7F", 6
 #define _STOPHn "7F", 5

 #define _STOPV  "7F", 8
 #define _STOPVn "7F", 9

 #define _AV1 "5H", 14
 #define _AV2 "5H", 13
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 #define _MH3 "4K", 12
 #define _MH4 "4K", 11

 #define _AVWIN "5L", 7
 #define _AHWIN "4K", 15

 #define _SWLEFTn "8J", 10

 #define _JOYLEFT  "XF", 2
 #define _JOYRIGHT "XF", 4
 #define _JOYUP    "XF", 6
 #define _JOYDOWN  "XF", 8


//Large fish motion
 #define _LRGFISHDIR "8J", 12

 #define _BV1 "2K", 14
 #define _BV2 "2K", 13
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 #define _LH3 "4M", 11
 #define _LH4 "3N", 3

 #define _LVWIN "3M", 11
 #define _LHWIN "3N", 2

 #define _VAEQB "3J", 6

//Image generation
 #define _D1 "1DA", 12
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 #define _XD7 "XC", 12   //temp fix for 2 roms joined
 #define _XD8 "XC", 10   //temp fix for 2 roms joined

 #define _LD1An "3B", 3
 #define _LD1Bn "3B", 4
 #define _LD1Cn "3B", 5
 #define _LD2An "3B", 10
 #define _LD2Bn "3B", 11
 #define _LD2Cn "3B", 12

 #define _SHARKENABLEn "7N", 8
 #define _DIVERENABLEn "5N", 10

 #define _MEDFISH "3C", 10
 #define _DIVERVID "3D", 8
 #define _LRGFISH "3E", 10
 #define _LRGFISHVID "3D", 6
 #define _SMLFISH "3C", 13
 #define _SMLFISHVID "3D", 11

 #define _V4 "1H", 4
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 #define _V1 "1H", 9

//Catch
 #define _CATCH "8L", 10

 #define _RESET "6H", 9
 #define _RESETn "6H", 8

//#define _RESETn VCC  //test

//#define _D1 "Z1", 4   //join 2 rom outputs
//#define _D2 "Z1", 7 
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 CONNECTION("LATCH", 3,  "8F", 9)

 CONNECTION(VCC,         "N9A", 4)
 CONNECTION(_STARTn,     "N9A", 2) // 556 pin 6


/* half second clock (page 1 A-8) */
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CONNECTION("VIDEO", 3, _LRGFISHVID)  //large fish=shark
CONNECTION("VIDEO", 4, _SMLFISHVID) 
CONNECTION("VIDEO", 5, VCC) 
CONNECTION("VIDEO", Video::VBLANK_PIN, "4A", 3)
CONNECTION("VIDEO", Video::HBLANK_PIN, "5A", 6) 

//CONNECTION("VIDEO", 2, _MEDFISH)  //medium fish=diver=player 
//CONNECTION("VIDEO", 3, _LRGFISH)  //large fish=shark
//CONNECTION("VIDEO", 4, _SMLFISH)
//CONNECTION("VIDEO", Video::VBLANK_PIN, _VBLANK)
//CONNECTION("VIDEO", Video::HBLANK_PIN, _HBLANK) 


/* Invert joystick so that pressed=HI and unpressed=LO */
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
